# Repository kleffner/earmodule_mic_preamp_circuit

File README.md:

# Ear Module Mic Pre-Amp Circuit
* Author: Matt Kleffner
* License: CC BY-SA 4.0 or Later

# Requirements:
* Interface hearing-aid mems microphones to sound card
* Low power
* Low noise, less than or equal to EIN of mic
* High-impedance interface
  * Mic output impedance on the order of 5 kOhm
* 100 Ohm output to drive high-impendance sound cards
* Single-ended input
* Differential output
* 1V Mic-bias supply needed
* Bi-polar AA power supply, +/- 3.2V, operate down to +/- 2V
* Op-amps provide clean 3.5V swing at +/- 2V supply

# Filter Gain Requirements
* Typical mic sensitivity is -38 dB re 1V/Pa or approx. 0.0125 V/Pa
* 120 dB is 20 Pa (10^(120/20)*20e-6)
* Mic output voltage at 120 dB is 20 Pa * 0.0125 V/Pa = 250 mV
* Gain for 120 V -> 3.5 V is 3.5/.250 = 14
* Allow for overshoot and set gain to 7
* Set input impedance to 20K, which is feedback impedance of 140K
  * Higher input impedances could increase circuit noise
* Mic output voltage will be scaled to approx 20/(20+5) or 20% reduction
* Match resistance seen on both + and - terminals
* 20K//140K = 17.5K - not available, but lots of 17.4K and 100 are

# Filter Cutoff Requirements
* Cost-effective, tight tolerances are 0.1% resistors, 5% capacitors
* Low cutoff < 20Hz, including tolerances
  * R = 20K, C=0.47e-6 gives (min,nom,max) cutoff of (16.1, 16.9, 17.8) Hz
* High cutoff > 20kHz, including tolerances
  * R = 140K, C=51pF gives (min,nom,max) cutoff of (21.2, 22.3, 2.35) kHz

# Op-amp selection
* Input stage
  * Implements filter
  * Low-noise
  * Low output impedance
  * Candidates
    * ADA4807
    * ADA4177
    * ADA4661 seems to be the best selection for the constraints

* Differential output stage
  * Requirements:
  * Unity-gain
  * Single-to-differential operation
  * Built-in over-voltage protection
  * Low-noise
  * Accurate differential-input impedance
  * Use ADA8476
    * Matched to <0.05% error
    * Protection to over 18V 

# Voltage regulator
* Low-noise
* Low component count
* TPS7A2010 Looks good but doesn't seem available in desired package
* TLV71210 is close, use it

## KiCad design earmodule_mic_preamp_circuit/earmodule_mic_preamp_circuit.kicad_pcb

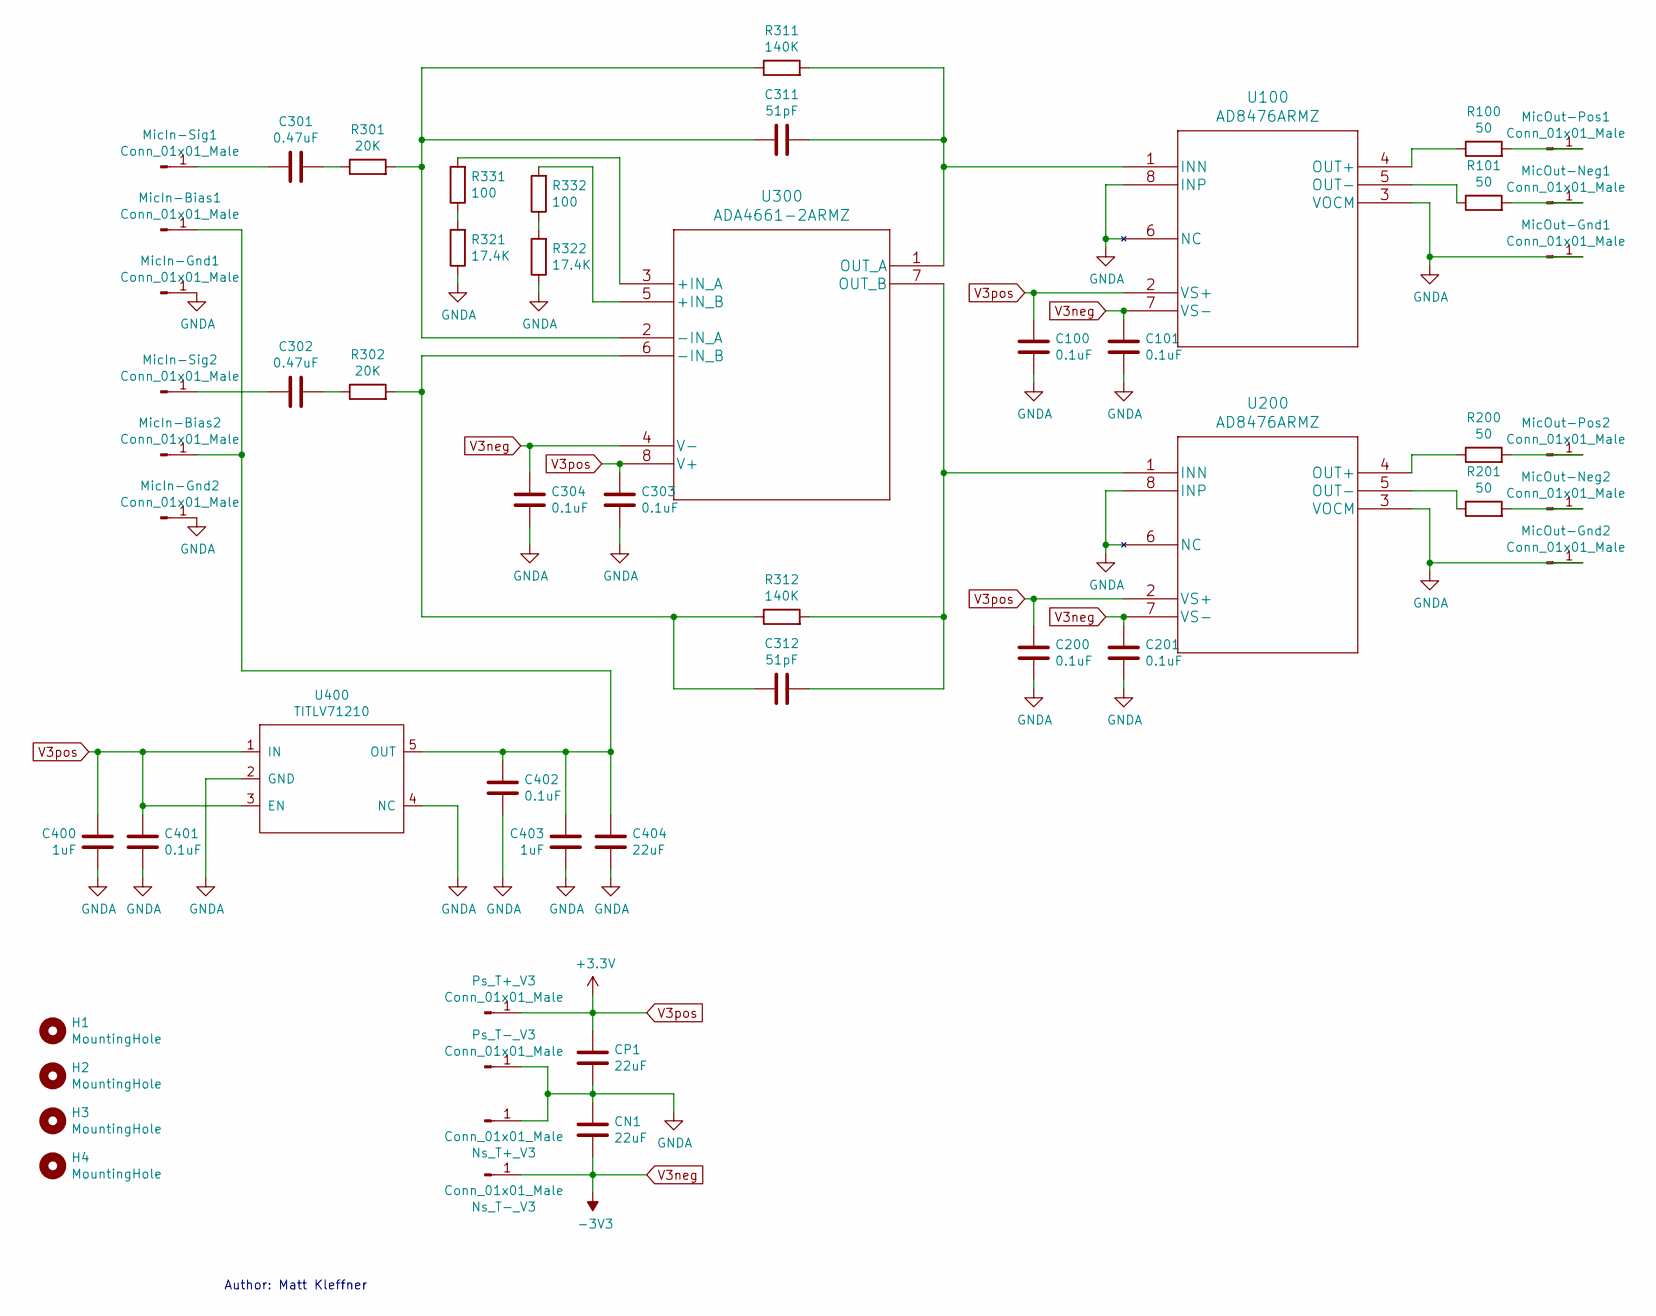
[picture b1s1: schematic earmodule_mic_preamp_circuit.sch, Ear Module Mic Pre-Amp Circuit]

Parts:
C100, C101, C200, C201, C303, C304, C401, C402: 0.1uF; C_0402_1005Metric
C301, C302: 0.47uF; C_0402_1005Metric
C311, C312: 51pF; C_0402_1005Metric
C400, C403: 1uF; C_0805_2012Metric_Pad1.15x1.40mm_HandSolder
C404: 22uF; C_1206_3216Metric_Pad1.42x1.75mm_HandSolder
CN1: 22uF; C_1206_3216Metric_Pad1.42x1.75mm_HandSolder
CP1: 22uF; C_1206_3216Metric_Pad1.42x1.75mm_HandSolder
H1, H2, H3, H4: MountingHole; MountingHole_2.7mm_M2.5_ISO7380
MicIn-Bias1, MicIn-Bias2: Conn_01x01_Male; TestPoint_Pad_D4.0mm
MicIn-Gnd1, MicIn-Gnd2: Conn_01x01_Male; TestPoint_Pad_D4.0mm
MicIn-Sig1, MicIn-Sig2: Conn_01x01_Male; TestPoint_Pad_D4.0mm
MicOut-Gnd1, MicOut-Gnd2: Conn_01x01_Male; TestPoint_Pad_D4.0mm
MicOut-Neg1, MicOut-Neg2: Conn_01x01_Male; TestPoint_Pad_D4.0mm
MicOut-Pos1, MicOut-Pos2: Conn_01x01_Male; TestPoint_Pad_D4.0mm
Ns_T+_V3: Conn_01x01_Male; TestPoint_Pad_D4.0mm
Ns_T-_V3: Conn_01x01_Male; TestPoint_Pad_D4.0mm
Ps_T+_V3: Conn_01x01_Male; TestPoint_Pad_D4.0mm
Ps_T-_V3: Conn_01x01_Male; TestPoint_Pad_D4.0mm
R100, R101, R200, R201: 50; R_0402_1005Metric
R301, R302: 20K; R_0402_1005Metric
R311, R312: 140K; R_0402_1005Metric
R321, R322: 17.4K; R_0402_1005Metric
R331, R332: 100; R_0402_1005Metric
U100, U200: AD8476ARMZ
U300: ADA4661-2ARMZ
U400: TITLV71210; SOT-23-5_HandSoldering

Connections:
GNDA: C100.2, C101.2, C200.2, C201.2, C303.2, C304.2, C400.2, C401.2, C402.2, C403.2, C404.2, CN1.1, CP1.2, MicIn-Gnd1.1, MicIn-Gnd2.1, MicOut-Gnd1.1, MicOut-Gnd2.1, Ns_T+_V3.1, Ps_T-_V3.1, R321.1, R322.1, U100.3 (VOCM), U100.6 (NC), U100.8 (INP), U200.3 (VOCM), U200.6 (NC), U200.8 (INP), U400.2 (GND), U400.4 (NC)
unnamed: C301.1, R301.1
unnamed: C301.2, MicIn-Sig1.1
unnamed: C302.1, R302.1
unnamed: C302.2, MicIn-Sig2.1
unnamed: C311.1, R311.2, U100.1 (INN), U300.1 (OUT_A)
unnamed: C311.2, R301.2, R311.1, U300.2 (-IN_A)
unnamed: C312.1, R312.2, U200.1 (INN), U300.7 (OUT_B)
unnamed: C312.2, R302.2, R312.1, U300.6 (-IN_B)
unnamed: C402.1, C403.1, C404.1, MicIn-Bias1.1, MicIn-Bias2.1, U400.5 (OUT)
unnamed: MicOut-Neg1.1, R101.2
unnamed: MicOut-Neg2.1, R201.2
unnamed: MicOut-Pos1.1, R100.2
unnamed: MicOut-Pos2.1, R200.2
unnamed: R100.1, U100.4 (OUT+)
unnamed: R101.1, U100.5 (OUT-)
unnamed: R200.1, U200.4 (OUT+)
unnamed: R201.1, U200.5 (OUT-)
unnamed: R321.2, R331.1
unnamed: R322.2, R332.1
unnamed: R331.2, U300.3 (+IN_A)
unnamed: R332.2, U300.5 (+IN_B)
V3neg: C101.1, C201.1, C304.1, CN1.2, Ns_T-_V3.1, U100.7 (VS-), U200.7 (VS-), U300.4 (V-)
V3pos: C100.1, C200.1, C303.1, C400.1, C401.1, CP1.1, Ps_T+_V3.1, U100.2 (VS+), U200.2 (VS+), U300.8 (V+), U400.1 (IN), U400.3 (EN)

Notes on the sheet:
Author: Matt Kleffner

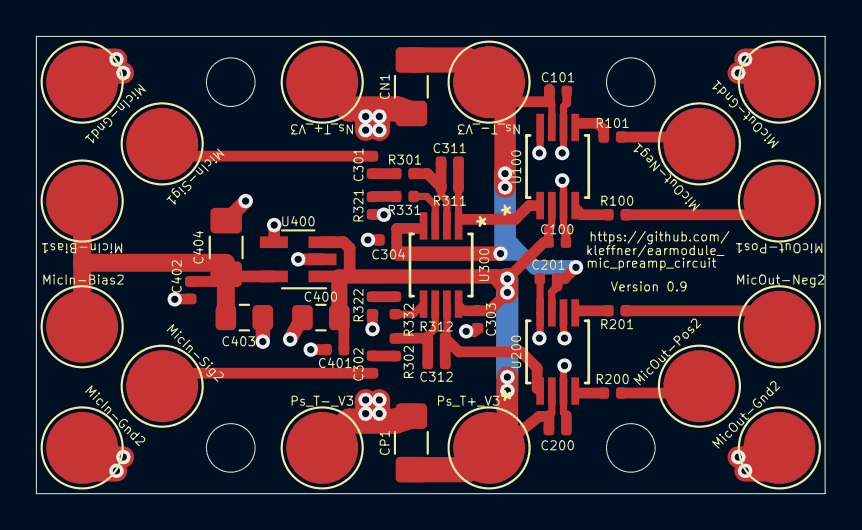
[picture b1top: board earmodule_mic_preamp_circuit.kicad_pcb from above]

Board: 2 copper layers, 43.8 x 25.4 mm, 53 parts (0 on the bottom side), 24 nets.

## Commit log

2021-03-01 Initial circuit design and schematic capture
2021-08-17 First complete PCB layout. Silkscreen needs to be fixed.
2021-08-18 Shrink and position silkscreen
2021-08-26 Rearranged regulator layout for better co-location of parts. Cleaned up interface names.
2021-09-01 Enlarged board and wire solder pad sizes. Added small decoupling caps in bias circuit. Finalized naming, numbering, and placement of text.
2021-09-02 Corrected miminum solder mask width. Aligned traces and copper fill along board edge to statisfy minimums. Removed backup file from repo.

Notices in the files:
parts and their libraries:
Copyright 2016 Accelerated Designs. All rights reserved.
